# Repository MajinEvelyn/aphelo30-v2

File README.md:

# aphelo30

Pictured with KLP Lame keycaps that I dyed with [Rit Synthetic Dye](https://www.ritdye.com/type/dyemore-for-synthetics/) using [this method](https://blog.zsa.io/how-to-dye-keycaps/). Case printed in Dark Red PLA.

## Design Parameters
- Full split
- ZMK powered BLE wireless
- Nice! Nano v2 controlled
- Reversible PCB
- 30 keys in 3x5 configuration
- Choc v1 Switches with hotswap sockets
- No thumb keys
- Middle, ring, and pinky splay

Named for the *Aphelocoma* genus of scrub jay birds, like the original. 

## Overview

This weird combination of features is designed for my hands, which no currently existing boards accommodate. I have RSI issues in both of my thumbs, to the point that even single thumb key layouts don't work for me. Aside from this, the aggressive splay and finger positions were made with Ergopad, and recreated in Ergogen. 

Compared to the first version of this keyboard, I adjusted the splay, overall key position, power and reset button positions, and adjusted the PCB and case to accomodate magnetic USB connectors, which I find very convenient. Additionally, instead of a carrying case using a sliding design, this project uses a much more compact magnetic cover to sandwich between both halves.

In this repo you will find all files related to the design process, including the Ergogen config, KiCAD PCB files, related Gerbers, and case 3d files for printing. 

## Case

There are 4 bosses for heat set inserts on the underside of each half's top case. Press them into each boss with a soldering iron, and use your M2 screws through the holes in the bottom case to screw into the heat set inserts.
There are heat set insert soldering tips available for pretty cheap to make this process easy, but I've heard this is easy enough with typical soldering iron tips.

This case, and PCB is designed with the magnetic USB adapters linked in the BOM, and they sit very flush with the side once assembled. I doubt that other connectors would sit flush in the same way without adjustments to the case design.

The magnets are secured in the cutouts using adhesive, in my case I used B-7000 Clear glue.

## Carrying Case

This "case" is more of a magnetically attached sandwich cover for the keycaps, and with this arrangement of magnets is very strong. I easily slide into a slot in my camera bag for work.

## Firmware
ZMK: https://github.com/MajinEvelyn/zmk-config-aphelo30
This is the same firmware as the first version, it is fully compatible with both with no changes.

## BOM

| Name | Count | Notes |
| ---- | ----- | ---------- |
| PCB | 2 | These are reversible, so either PCB works with either half. |
| Nice! Nano v2 MCU | 2 | |
| Choc v1 Switches | 30 | |
| Choc v1 Hotswap Sockets | 30 | |
| Choc v1 Keycaps | 30 | |
| Power Switch | 2 | |
| Reset Switch | 2 | You can omit these if you are fine with using ZMK reset behavior or shorting RST pins to reflash firmware. |
| 110mah LiPo Battery | 2 | There is plenty of space for other batteries inside the case, but these can sit underneath the nice! nano. |
| Bumpons | 12 | Size is up to your preference. |
| M2(x8mm) Screws | 8 | Countersunk screws are best, they will seat perfectly into the chamfered holes in the bottom case. |
| M2 Heat Set Inserts | 8 | |
| Magnetic USB C adapters | 2 | https://a.co/d/0hXRvKBZ |
| 5 mm x 1 mm Neodynium Magnets | 16 | https://amfmagnets.com/products/neodymium-disc-5-mm-x-1-mm-gold |

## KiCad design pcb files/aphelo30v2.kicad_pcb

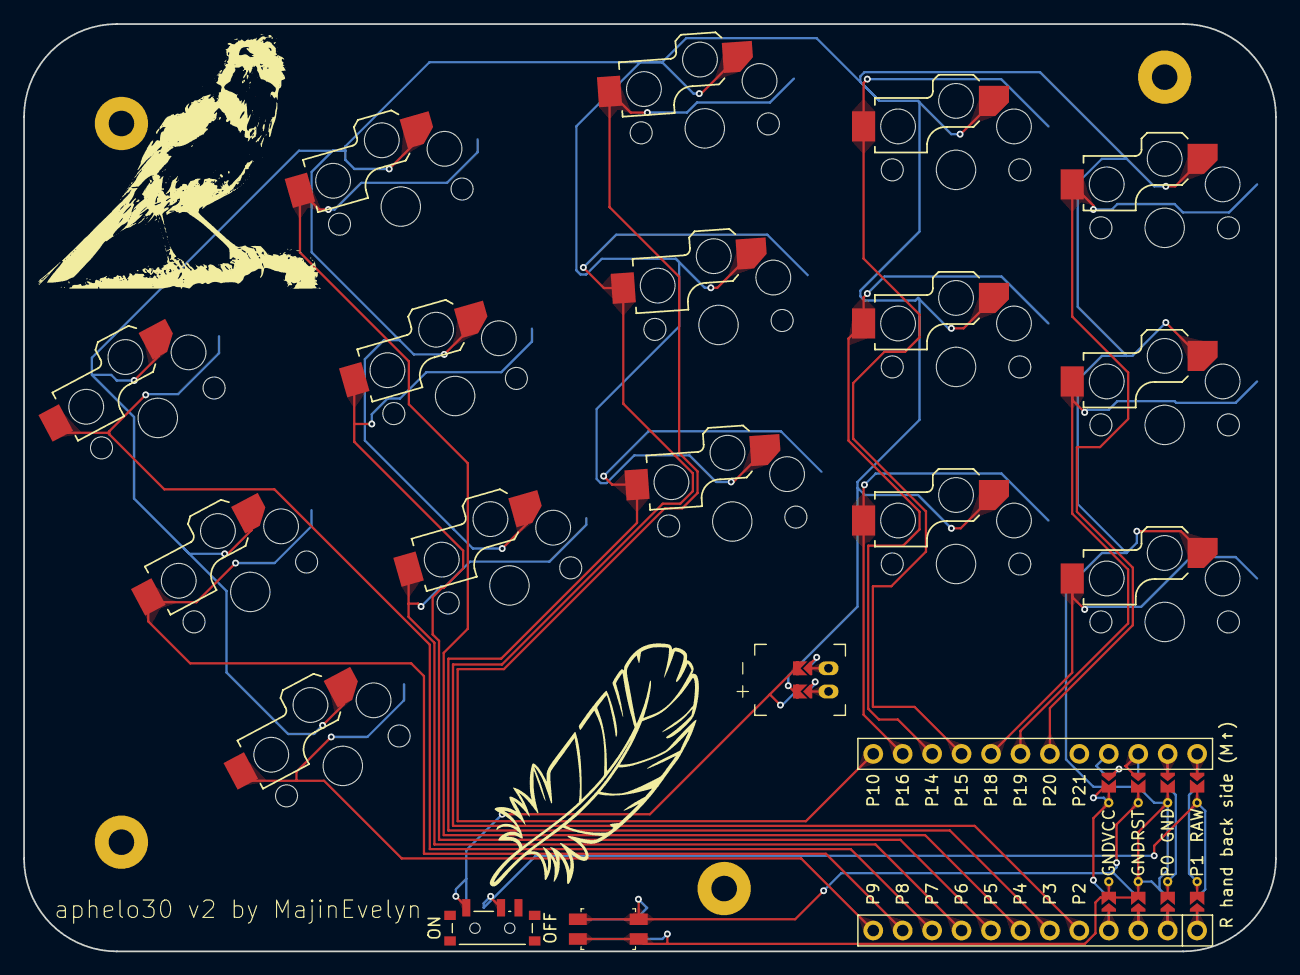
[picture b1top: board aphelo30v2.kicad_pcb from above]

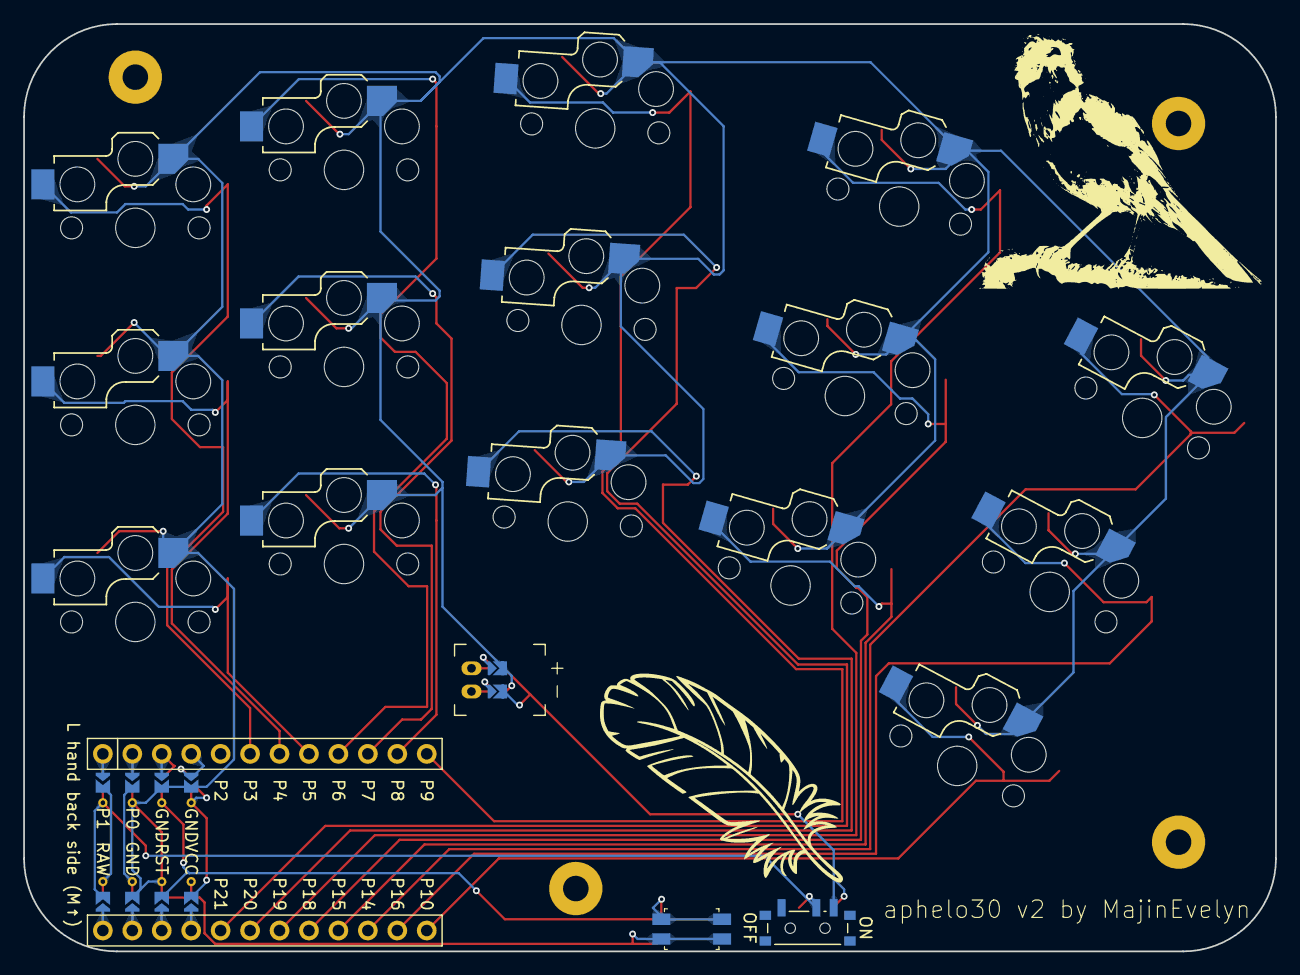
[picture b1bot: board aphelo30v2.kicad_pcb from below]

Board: 2 copper layers, 108.0 x 80.0 mm, 23 parts (15 on the bottom side), 21 nets.

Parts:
JST1: battery_connector_jst_ph_2
MCU1: mcu_nice_nano
MH1, MH2, MH4, MH5: mounting_hole_npth
PWR1: power_switch_smd_side
RST1: reset_switch_smd_side
S1, S2, S3, S4, S5, S6, S7, S8, S9, S10, S11, S12, S13, S14, S15: switch_choc_v1_v2

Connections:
BAT_P: JST1.1, PWR1.1, PWR1.3
GND: JST1.2, MCU1.103, MCU1.104, MCU1.123, RST1.1, RST1.3, S1.1, S2.1, S3.1, S4.1, S5.1, S6.1, S7.1, S8.1, S9.1, S10.1, S11.1, S12.1, S13.1, S14.1, S15.1
JST1_1: JST1.11, JST1.21, JST1.31
JST1_2: JST1.12, JST1.22, JST1.32
P2: MCU1.5, S8.2
P3: MCU1.6, S7.2
P4: MCU1.7, S6.2
P5: MCU1.8, S5.2
P6: MCU1.9, S4.2
P7: MCU1.10, S3.2
P8: MCU1.11, S2.2
P9: MCU1.12, S1.2
P10: MCU1.13, S9.2
P14: MCU1.15, S11.2
P15: MCU1.16, S12.2
P16: MCU1.14, S10.2
P18: MCU1.17, S13.2
P19: MCU1.18, S14.2
P20: MCU1.19, S15.2
RAW: MCU1.124, PWR1.2
RST: MCU1.122, RST1.2, RST1.4

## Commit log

2026-06-26 Rename DSCF4149.JPG to img/DSCF4149.JPG
2026-06-26 Rename P6260229.JPG to img/P6260229.JPG
2026-06-26 Revise README for aphelo30 keyboard specifications
    Updated README to reflect new design and features for the aphelo30 keyboard, including images, design parameters, overview, case details, firmware link, and BOM.
2026-06-26 Fix image links in README.md
    Updated image links in README.md to use 'blob' instead of 'tree' for correct display.
2026-06-26 Rename aphelo30 v2 case bottom 1.2.3mf to case files/aphelo30 v2 case bottom 1.2.3mf
2026-06-26 Rename aphelo30 v2 case bottom right 1.3.3mf to case files/aphelo30 v2 case bottom right 1.3.3mf
2026-06-26 Rename aphelo30 v2 case top 1.2.3mf to case files/aphelo30 v2 case top 1.2.3mf
2026-06-26 Rename aphelo30 v2 magnet cover 1.2.3mf to case files/aphelo30 v2 magnet cover 1.2.3mf
2026-06-26 Rename aphelo30v2.step to pcb files/aphelo30v2.step
2026-06-26 Add images to README for better visualization
2026-06-26 Update README to simplify design process description
    Removed information about PCB footprint size and cost estimation.
